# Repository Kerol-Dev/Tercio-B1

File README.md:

<div align="center">

# Tercio B1

**Brushless FOC on the Tercio bus.**

A 46 × 46 mm field-oriented-control driver for gimbal, quasi-direct-drive and hobby brushless motors.<br>
10–52 V, a 21-bit encoder on board, and the same bus, browser panel and libraries as the Tercio S1.

**Rev A is designed and 100 % routed, and its firmware runs on a simulated motor. Nothing has run on real hardware yet:<br>every rating on this page is a design target until the [bench tests](docs/08-bringup.md) confirm it.**

[Hardware](hardware/README.md) ·
[Firmware](firmware/README.md) ·
[Simulator](#simulator) ·
[Spec vs moteus](docs/02-spec-vs-x1.md) ·
[Plan](#documents)

</div>

---

## Why

A Tercio machine can already put closed-loop steppers and an IMU on one CAN bus, set up from a browser. Some joints want a brushless motor instead: gimbals that must be smooth at a crawl, legs and arms on quasi-direct-drive actuators, anything that needs torque control rather than position alone.

Good brushless controllers exist, but each comes with its own adapter, its own tools and its own library. The Tercio B1 joins the bus you already have. It speaks Tercio protocol v2 as device class 2, appears in Tercio Control next to your S1 drivers and IMUs, and is driven from the same Python and Arduino libraries. It aims at the mjbots moteus-x1 and moteus-n1 on that ecosystem and on value: a target of $99–119.

## Highlights (design targets)

| | |
|---|---|
| **On the Tercio bus** | Protocol v2, device class 2. Discovery, node IDs, parameters, telemetry and fault events work as on the S1, through the same Tercio FD adapter. |
| **21-bit encoder on board** | An MT6835 sits on the shaft axis under the board. The aux port takes an output-side encoder (SPI, I²C or quadrature), step/dir, RC PWM and a motor NTC. |
| **10–52 V, 80 V FETs** | A DRV8353RS 100 V-class gate driver with drain-source over-current protection, six 80 V / 3 mΩ BSC030N08NS5, 1 mΩ Kelvin shunts, and a regen clamp in firmware from day one. |
| **Fast loops** | PWM at 15–40 kHz (30 kHz by default), the current loop at the PWM rate, the position or velocity loop every second tick. |
| **Calibrates itself** | Measures current-sense offsets, resistance, inductance, pole pairs, direction, encoder offset and flux linkage. In simulation, R, L and flux linkage come out within 1 % on the 5010 and 2204 test motors; the gimbal's resistance reads 3.5 % high. |
| **Both bus speeds** | 500 k / 2.5 Mbit/s and 1 M / 5 Mbit/s bus profiles from the first release. |
| **Generated by code** | Schematic, placement, copper and routing are all Python that writes KiCad 10 files, authored by AI, and checked by KiCad itself: ERC 0, DRC 0, 0 schematic-parity issues. |

## Rev A board

- **46 × 46 mm, 6 layers**: 2 oz outer and 1 oz inner copper, 1.6 mm, matte black ENIG, filled and capped vias in pads.
- **Top:** the XT30 on the left edge; three half-bridges across the lower half, each low-side FET with its Kelvin shunt; phase pads A/B/C on the bottom edge; the DRV8353RS above them with its 5 V buck; CAN-in, aux and CAN-out connectors on the edges; status LEDs.
- **Bottom** (faces the motor, ≤ 2.3 mm parts): the MT6835 on the shaft axis, the STM32G431 beside the gate driver, the CAN transceiver between the connectors, SWD pads and a named test point for every rail and phase.
- **Numbers:** 163 footprints, 1,237 tracks, 340 vias, 100 % routed. BOM: 54 lines, every part in stock at JLCPCB when checked on 2026-10-13, $26.08 per board at 10 and $22.44 at 100 (components).
- **Fabrication:** `hardware/tools/jlc_fab.py` writes the gerbers, BOM and placement file for JLCPCB assembly.

## How it works

```mermaid
flowchart LR
    BUS["CAN FD bus<br/>Tercio protocol v2"] --- CAN["MCP2562FD"]
    CAN --- MCU["STM32G431<br/>FOC at 30 kHz"]
    ENC["MT6835<br/>21-bit encoder"] -- "SPI" --> MCU
    MCU -- "6 × PWM" --> DRV["DRV8353RS<br/>gate driver + 3 current amps"]
    DRV --> FET["3 half-bridges<br/>6 × BSC030N08NS5"]
    PWR["XT30<br/>10–52 V"] --> FET
    FET --> MOT(("Motor"))
    FET -. "1 mΩ Kelvin shunts" .-> DRV
    DRV -- "phase currents" --> MCU
```

- **One call per PWM period.** `FocCore` takes the ADC sample and returns the duties: Clarke and Park transforms, a d/q current controller with decoupling and latency compensation, space-vector PWM and per-tick protection. It is plain C++ with no HAL, so the same code runs on the MCU, in the unit tests and in the simulator.
- **The joint.** `Joint` runs the protocol-v2 states, the position, velocity, torque and impedance modes on the S1's trajectory planner, the regen clamp, a 1 s host deadman and temperature derating.
- **Shared with the S1.** The trajectory planner and the encoder tracker come from the S1 firmware; the CAN node and the wear-levelled settings will too ([docs/07](docs/07-firmware.md) §7.3), so the B1 behaves like the rest of the Tercio bus.

## Simulator

The firmware above, unchanged, runs at 30 kHz in real time against a model of the motor and the board.

- **The model:** a dq motor with cogging and friction, dead time, a supply that cannot sink current, 12-bit current-sense codes, the encoder's noise and timing, and the gate driver's over-current latch.
- **The page:** pick a motor, run the calibration and see what it found next to the true values, then move the joint and watch the scope at 1 kHz, or one PWM period at a time.
- **Testing:** inject faults, load the shaft, or drag the rotor by hand.

```bash
cd firmware
node simulator/server.mjs             # http://127.0.0.1:8770, builds the simulator first if needed
```

## Specifications (design targets)

| | |
|---|---|
| **Supply** | 10–52 V (3S–12S, 48 V supplies); input TVS SMCJ54A; over-voltage fault ≤ 58 V |
| **Phase current** | ~80 A peak by design; 15 A continuous without cooling as the target. Both are published only after measurement. |
| **PWM and current loop** | 15–40 kHz, 30 kHz by default |
| **MCU** | STM32G431CBT6, Arm Cortex-M4F at 170 MHz (STM32G474CBT6 as a pin-compatible alternate) |
| **Power stage** | DRV8353RS, 6 × BSC030N08NS5 (80 V, 3.0 mΩ), 1 mΩ 2512 Kelvin shunts |
| **Encoder** | MT6835, 21-bit absolute, on board |
| **Aux port** | JST-GH 8: SPI, I²C, quadrature, step/dir, RC PWM, GPIO, motor NTC, 3.3 V (PTC-limited) |
| **Bus** | CAN FD, 500 k / 2.5 Mbit/s and 1 M / 5 Mbit/s, Tercio protocol v2; 2 × JST-GH 4 for daisy chaining; 120 Ω termination by solder jumper |
| **Power connector** | XT30 (right angle) and phase solder pads |
| **Board** | 46 × 46 mm, 6 layers, height ≤ 10 mm target, ≤ 16 g target |
| **Host tools** | Tercio Control in the browser and the Python and Arduino libraries, through the Tercio FD |

The comparison with moteus-x1, n1 and r4.11 is in [docs/02](docs/02-spec-vs-x1.md).

## Building it

### Firmware

```bash
cd firmware
~/.platformio/penv/bin/pio test -e native     # host tests on simulated motors
```

### Hardware

```bash
python3 hardware/build.py                      # schematic → netlist check → ERC → PDF
python3 -I hardware/verify_bom.py              # every LCSC code checked live against JLCPCB
```

The board scripts need KiCad 10's own Python, for `pcbnew`:

```bash
KPY=/Applications/KiCad/KiCad.app/Contents/Frameworks/Python.framework/Versions/3.9/bin/python3
cd hardware
$KPY layout.py                                 # place, copper, route, fill, DRC, renders
$KPY tools/jlc_fab.py                          # build/jlc: gerbers, BOM, CPL for JLCPCB
```

The files in `hardware/kicad/` are generated: change the code and regenerate rather than editing them in KiCad. The full flow, the router and the checks are in [hardware/README.md](hardware/README.md).

## Status and next steps

| | |
|---|---|
| **Done** | Plan and decisions; rev A schematic, board and routing, DRC clean; JLC fabrication files; firmware milestone F0 (FOC core, calibration, joint) with host tests 1–6 and the real-time simulator |
| **Next** | Regen and fault-reaction tests in simulation; the CAN and protocol layer; bring-up firmware; order rev A |
| **Schedule** | Rev A order around 21 December 2026, rev B after Chinese New Year, launch around June 2027 ([docs/09](docs/09-risks-schedule.md)) |
| **Guardrail** | The Tercio S1 and FD launch on 1 December 2026 comes first: no B1 changes to the other Tercio repositories before then, and a B1 freeze from 23 November to 7 December |

## Documents

| # | Document | Contents |
|---|---|---|
| 1 | [Requirements and the wedge](docs/01-requirements.md) | Decisions, functional requirements, positioning against moteus/ODrive, rating method |
| 2 | [Spec versus moteus-x1](docs/02-spec-vs-x1.md) | Side-by-side with x1, n1 and r4.11 |
| 3 | [Part shortlist](docs/03-parts.md) | Live LCSC/JLCPCB stock and prices (2026-10-12), choices and alternates |
| 4 | [Block diagram and pin map](docs/04-architecture.md) | Power tree, STM32G431 pin map, TIM1/ADC sync, aux and CAN connectors, floor plan |
| 5 | [BOM cost and PCB plan](docs/05-bom-pcb.md) | Planning estimate ≈ $45/board at 10, ≈ $25.50 at 100 (landed); stackup and layout rules |
| 6 | [KiCad as code](docs/06-kicad-as-code.md) | Python-generated schematic and board, routing, kicad-cli checks and outputs |
| 7 | [Firmware plan](docs/07-firmware.md) | S1 architecture reuse, FOC core, calibration and identification, protocol additions, bus profiles, host simulator |
| 8 | [Bring-up and test plan](docs/08-bringup.md) | Equipment, regen handling, 14 staged tests with pass criteria |
| 9 | [Risks and schedule](docs/09-risks-schedule.md) | Risk register; 3 spins; launch ~June 2027; ≈ $4,000–4,500 to launch |

## Repository layout

```text
docs/        the plan: requirements, spec, parts, architecture, BOM, KiCad as code, firmware, bring-up, risks
data/        live part data, BOM estimate, pin map
tools/       part lookup (JLCPCB + LCSC), BOM estimate, CAN bus-time budget
hardware/
├── b1/      the Tercio B1 circuit, one module per sheet; placement, copper, routing plan, silkscreen
├── gen/     the generator: KiCad file writer, symbols, footprints, board engine, router
├── tools/   JLCPCB fabrication files, routing report, XT30 3D model
├── kicad/   the generated KiCad 10 project (open tercio-b1.kicad_pro to review)
└── lib/     IBM Plex fonts for the silkscreen (project footprints and symbols are in kicad/lib/)
firmware/
├── src/     foc/, control/, app/ (MCU and host); sim/, simulator/ (host only)
├── simulator/  Node server and web UI
└── test/    host tests
```

## Data and tools

| Path | What |
|---|---|
| `tools/parts_lookup.py` | Live JLCPCB + LCSC stock and price lookup (standard library only). Reads `tools/candidates*.txt` |
| `tools/bom_estimate.py` | BOM cost at 10/100 boards from the lookup data → `data/bom-estimate.csv` |
| `tools/can_budget.py` | CAN FD bus-time budget per node and rate (`python3 tools/can_budget.py 1000000 5000000`) |
| `data/parts-live-2026-10-12*.csv` | 686 rows of live part data from 2026-10-12 |
| `data/pinmap-g431cbt6.csv` | Pin map as a table, for the generator |

Re-run before any order (stock moves daily):

```bash
python3 -I tools/parts_lookup.py && python3 -I tools/parts_lookup.py tools/candidates-extra.txt && python3 -I tools/bom_estimate.py
```

## Decision log

Decided with Kerol on 2026-10-12:

| Topic | Decision |
|---|---|
| Power class | Smaller class first → 10–52 V (DRV8353RS makes 12S/48 V possible) |
| Peak current | Design for ~80 A peak; lead marketing with continuous current |
| Target motors | Gimbal, QDD 5010/6010, small drone/hobby BLDC |
| Price | $99–119 |
| Size | ~46 × 46 mm |
| Encoder | Onboard MT6835 (21-bit) + aux port for an output-side encoder |
| MCU | STM32G431CBT6 (G474CBT6 as a pin-compatible alternate) |
| Gate driver | DRV8353RS |
| CAN connector | 2 × JST-GH 4-pin, daisy chain |
| Power connector | 1 × XT30 + motor solder pads |
| Extras | Motor thermistor, PWM and step/dir input, spare GPIO/analog |
| USB | No (CAN only, via the FD) |
| Bus | 500k/2.5M and 1M/5M, both from the B1's first release |
| Licence | Apache-2.0 |
| Name | Tercio B1 |
| KiCad flow | Code owns everything, including routing |
| Timing | Start the schematic now, in parallel with the launch |
| S1 and the 1M/5M bus | No S1s are built yet: the shipping firmware carries the bus profile |
| Repository | Private GitHub repo Kerol-Dev/Tercio-B1 (named Tercio-bldc until 2026-10-18) |

Still open:

| Topic | Notes |
|---|---|
| Weekly time cap before launch | Yours to set; the schedule assumes part-time |
| Electrolytic on board vs on the XT30 pigtail | Height (10 mm) vs cable damping. Rev A carries a 22 µF 100 V can on board |
| Mounting-hole pattern | Check against the 5010/6010 motors on rev A |
| Retail price inside $99–119, volume tiers, starter bundle | After rev B, when the BOM and ratings are firm |

## Licence

Apache-2.0, see [LICENSE](LICENSE).

<div align="center">
<sub>Made by <a href="https://terciolabs.com">Tercio Labs</a></sub>
</div>

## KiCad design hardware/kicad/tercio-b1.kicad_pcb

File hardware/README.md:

# Tercio B1 hardware — KiCad as code

The schematic is generated by Python and checked by KiCad 10 itself. **Do not
edit the files in `kicad/` by hand.** Change the code, regenerate, and review.

```bash
cd ~/Documents/Projects/Tercio-B1 && python3 hardware/build.py
```

```bash
cd ~/Documents/Projects/Tercio-B1 && python3 -I hardware/verify_bom.py
```

`build.py` writes the KiCad project and then:

1. exports the netlist with `kicad-cli` and compares every net, pin by pin,
   with the circuit the code describes (a wire that lands on the wrong pin, or
   two nets that touch, fails the build);
2. runs ERC at all severities;
3. exports `build/tercio-b1-schematic.pdf`.

Then the board, generated with KiCad's own Python (it needs `pcbnew`):

```bash
cd ~/Documents/Projects/Tercio-B1 && /Applications/KiCad/KiCad.app/Contents/Frameworks/Python.framework/Versions/3.9/bin/python3 hardware/layout.py
```

`layout.py` loads every footprint from the KiCad netlist (reference, value, fields
and schematic path, so DRC can check schematic parity), places the fixed parts from
`b1/board.py`, auto-places the rest (courtyard- and hole-aware, per side; each part lands
on the line from the pin it serves toward where that signal goes next), draws the outline,
the power copper and planes from `b1/copper.py` and the art from `b1/art.py`, sets the
matte-black ENIG stackup and the net classes, then **routes the board**, adds the fills
(GND on F/In2/In3/B, +3V3 on In3 under the logic half), fills the zones and renders
`build/render-*.png`. `--no-route` stops after placement; `--route-only` routes the board
as placed.

```bash
cd ~/Documents/Projects/Tercio-B1/hardware && /Applications/KiCad/KiCad.app/Contents/Frameworks/Python.framework/Versions/3.9/bin/python3 layout.py --no-route && FASTROUTE_ROUNDS=30 /Applications/KiCad/KiCad.app/Contents/Frameworks/Python.framework/Versions/3.9/bin/python3 layout.py --route-only
```

### Routing

`gen/route_export.py` (KiCad's Python) turns the board and the plan in `b1/routing.py` into
flat arrays (`build/route/problem.npz` + `.json`); `gen/fastroute.py` solves them in a
separate Python 3.12 with numpy and Numba (`TERCIO_FAST_PY`, default: the NEMA23-Adapter
venv in the Tercio-s1 repo); the result comes back as ordinary locked tracks and vias.
Freerouting 2.5 left ~180 of ~300 connections unrouted here and knows nothing about gate
loops or Kelvin pairs, so the router is ours.

- 0.05 mm grid on F / In2 / In3 / B (In1 and In4 are solid GND: vias only). Widths and
  clearances per net class, exact distances plus a 0.04 mm margin, so DRC passes by
  construction. Wide classes neck down to 0.2 mm at small pads.
- Via-in-pad is allowed: JLC fills and caps vias in pads on 6-layer boards at no charge.
  Vias are 0.45/0.2 mm for logic, 0.5/0.25 gate, 0.6/0.3 supply, 0.7/0.35 power.
- Power pours are walls for other nets, except right around a connection's own pads.
- Negotiated congestion (PathFinder): every net is routed, overlaps cost more each round
  (present and history), and the nets still in conflict are routed again until nothing
  overlaps. Then legalisation drops the least important net of each remaining conflict and
  puts it back with everyone else's copper as walls; a rescue step rips up lower-priority
  nets that block what is still unrouted; anything left is promoted (within its tier) for
  another pass. Searches that run out of budget get one wider try.
- Pairs: SNx is drawn to SPx (Kelvin), the SHx return to GHx (small gate loop).

The solved routes are stored in `b1/routes.json` (`layout.py --save-routes`) and re-applied on
every regeneration, so the board rebuilds in under a minute and the router only adds what is
missing. After a placement change, move `b1/routes.json` aside and route again.

Plan and tiers (`b1/routing.py`): Kelvin pairs, gate loops, the buck's input loop (VIN → its 1 µF),
DRV supply and buck first; then a GND via per pad; +3V3 (0.25 mm), +3.3VA and the V_BUS feeds;
then the rest, shortest first. Net classes: logic and Kelvin 0.15/0.15 mm (JLC's minimum for 2 oz
outer copper, so no slack there), gate 0.2/0.2, supply 0.3/0.2, power 0.4/0.2.
A run takes about 5–10 minutes. Failures, if any, are listed in `build/route-failures.txt`.

### Silkscreen

`b1/art.py` draws it, in IBM Plex (the website's type) turned into filled polygons by
`gen/fonttext.py` from the WOFF files in `lib/fonts/` (SIL OFL, licence alongside), so nobody needs
the font installed and the gerbers carry exactly these shapes. Everything goes through a small
planner that keeps each item off pads, part bodies and footprint outlines, holes, the edge and
the other labels, searching outward from where it belongs; test-point labels must sit closer to
their own pad than to any other test point, and every test point reserves room for its label when
it is placed. Sizes stay at JLC's legend minimums or above (strokes ≥ 0.15 mm).

- Top (seen once the board is on a motor): the Tercio mark and "Tercio B1", phase letters A/B/C,
  CAN / AUX / CAN names at the connectors, "10–52 V" at the XT30, STATUS / FAULT at the LEDs.
- Bottom (bring-up): the identity with "FOC MOTOR DRIVER · 10–52 V · REV A", every test point
  named (VBUS, 5V, 3V3, 3VA, GND, SOA/SOB/SOC, GLA/GLB/GLC, SW, FLT), the SWD pad order, the
  solder jumpers (120R, NTC), CAN and AUX pinout tables, phase letters, an S/N field.

### Fabrication (JLCPCB)

```bash
cd ~/Documents/Projects/Tercio-B1/hardware && /Applications/KiCad/KiCad.app/Contents/Frameworks/Python.framework/Versions/3.9/bin/python3 tools/jlc_fab.py
```

writes `build/jlc/`: `tercio-b1-gerbers.zip` (6 copper layers, mask, paste, silk, outline,
PTH/NPTH Excellon, nothing else), `tercio-b1-bom.csv` (Comment, Designator, Footprint, LCSC),
`tercio-b1-cpl.csv` (Designator, Mid X, Mid Y, Layer, Rotation) and `ORDER.md` (order-form
settings). The gerbers follow JLC's KiCad 9 guide to the letter: X2 and netlist attributes on (JLC's
parser reads the layer functions and the board profile from them; with X2 off the upload came back
with no layers or size), absolute coordinates, Protel extensions, PTH and NPTH separate. BOM and CPL
come from the routed board, so they agree with each other and the gerbers. CPL positions are pad
centres in the gerbers' absolute coordinates; rotation is KiCad's angle (top) or 180° − angle (bottom) plus a per-package
zero-orientation correction from the community table kept with the Fabrication Toolkit plugin
(the same formula as Bouni's kicad-jlcpcb-tools). Packages without an entry are listed in
`ORDER.md` to confirm in JLC's placement preview.

`verify_bom.py` exports the JLC BOM (`build/bom-jlc.csv`) and checks every
LCSC code live against JLCPCB: it must exist, match the value and package,
and have stock for the build. It also reports today's component cost.

State at rev A generation (2026-10-13):

| Check | Result |
|---|---|
| Netlist vs intent | 104 nets match; 12 no-connects, all intentional |
| ERC (all severities) | 0 violations |
| DRV8353RS symbol vs TI pin table | 48/48 pins match |
| MT6835 symbol vs MagnTek pin table | 16/16 pins match |
| BOM | 54 lines, 24 Extended, all codes valid and in stock; $26.08/board at 10, $22.44 at 100 (components) |
| Independent review (2026-10-12) | No critical findings; 4 major + 7 minor fixed (VDRAIN/VM filters, SMCJ54A, 50 mA aux PTC, 5.0 V FB, MT6835 TEST, 1 A inductor, 1.5k SDO pull-up, 10 µF bulk MLCC) |
| Board | 163 footprints, 6 layers, **100 % routed** (1,237 tracks, 340 vias, `b1/routes.json`); KiCad DRC at all severities (silkscreen included): 0 violations, 0 unconnected, 0 schematic-parity issues |
| Fabrication | `tools/jlc_fab.py`: gerbers + drill, BOM (54 lines) and CPL (122 parts: 48 top, 74 bottom) for JLCPCB |

## Layout of the code

| Path | What |
|---|---|
| `gen/sexpr.py` | S-expression reader/writer for KiCad files |
| `gen/symbols.py` | Loads KiCad 10's symbol libraries (flattens derived symbols), pin geometry, `make_ic` for code-defined symbols |
| `gen/model.py` | Circuit model: sheets, parts, pin→net assignments; every visible pin must be assigned or marked `NC` |
| `gen/writer.py` | Model → `.kicad_sch`/`.kicad_pro`, project symbol library; deterministic UUIDs |
| `gen/footprints.py` | Project footprints (Kelvin 2512 shunt with net-tie sense pads, motor phase pad) |
| `gen/custom.py` | DRV8353RS and MT6835 symbols, from the vendor pin tables |
| `gen/catalog.py` | Footprints and LCSC codes (JLC Basic where possible) |
| `b1/*.py` | The Tercio B1 circuit, one module per sheet, with design notes on each sheet |
| `gen/pcb.py` | Board engine (KiCad Python): netlist → footprints, placement with collision search, zones, vias, tracks |
| `gen/router.py` | Board geometry and clearance rasters for the router (the first, slower router lives on here too) |
| `gen/route_export.py`, `gen/fastroute.py` | Routing problem export (KiCad Python) and the Numba negotiated-congestion router |
| `b1/routing.py` | Routing plan: tiers and order, pairs |
| `tools/route_report.py` | Routing review: per-net length / vias / layers for the critical classes, per-layer copper plots |
| `b1/board.py`, `b1/copper.py`, `b1/art.py` | Placement plan, power copper and planes, silkscreen (planner + design) |
| `gen/fonttext.py`, `lib/fonts/` | IBM Plex outlines (WOFF, SIL OFL) → silkscreen polygons |
| `tools/jlc_fab.py` | JLCPCB gerbers, BOM and CPL with rotation corrections |
| `tools/xt30pw_model.py` | CadQuery model of the XT30PW-M (KiCad 10 ships none) |
| `build.py`, `layout.py`, `verify_bom.py` | Generate and check |
| `kicad/` | Generated KiCad project (open `tercio-b1.kicad_pro` in KiCad 10 to review) |
| `build/` | Netlist, ERC report, PDF, BOM (git-ignored) |

## Sheets

| Page | Sheet | Refs |
|---|---|---|
| 2 | Power input and rails: XT30, TVS, bulk, V_BUS sense, 3.3 V LDO, +3.3VA filter, test points, holes | 1xx |
| 3 | Gate driver and buck: DRV8353RS, VDRAIN filter, charge pump, LM5008A buck (+5V), SPI/fault/enable pulls, bring-up test points | 2xx |
| 4 | Power stage: 3 half-bridges, Kelvin shunts, gate resistors, DNP snubbers, bulk bank, FET NTC, DNP phase-voltage taps | 3xx |
| 5 | MCU: STM32G431CBT6, decoupling, HSE, reset/BOOT0, SWD pads (1×5, S1/FD order), LEDs, ADC front-end, SPI source termination | 4xx |
| 6 | Encoder: MT6835 (CAL_EN on PC15) | 5xx |
| 7 | CAN-FD: MCP2562FD, ESD, split termination (solder jumper), 2 × JST-GH 4 | 6xx |
| 8 | Aux port: JST-GH 8, series R, ESD, PTC 3V3, motor-NTC pull-up | 7xx |

## Review workflow

Open `kicad/tercio-b1.kicad_pro` in KiCad 10 (or read `build/tercio-b1-schematic.pdf`).
Write findings down. Fixes go into `b1/*.py`, and then you regenerate. Edits made
in KiCad are overwritten by the next build, by design ("code owns everything").

## Board (rev A) at a glance

- 46 × 46 mm, 6 layers (2 oz outer / 1 oz inner), 1.6 mm, matte black mask, white silk, ENIG,
  filled and capped vias in pads.
- Top: XT30 on the left edge, three half-bridges across the bottom half (high-side over low-side,
  Kelvin shunt beside each low-side FET, 10 µF 100 V bulk in slots around them), phase pads A/B/C
  on the bottom edge, DRV8353RS centred above the legs with its buck, 22 µF 100 V can, right-angle
  JST-GH connectors with their cable entries at the edges (CAN-in GH-4 top left, aux GH-8 top
  right, CAN-out GH-4 on the right edge), status LEDs.
- Bottom (≤ 2.3 mm parts, faces the motor): MT6835 on the shaft axis (turned 180° so its SPI pins
  face the MCU); the MCU beside the DRV, rotated 180° so its PWM / chip-select pins face the DRV's
  control pins across a 3 mm via lane and its aux pins face the aux connector; CAN transceiver
  between the CAN connectors, LDO, logic passives, SWD pads, test points, input TVS, the Tercio mark.
- Copper: In1 and In4 solid GND; In2 V_BUS under the power half (a finger up to the XT30), a phase
  pour per leg down to its pad, signals and GND fill elsewhere; In3 signals, then +3V3 fill under
  the logic half and GND fill under the power half; per-leg V_BUS / phase / LSRC / GND-return pours
  on top; phase pours on the bottom.
- Next: upload `build/jlc/` to JLC for the quote, check the parts listed in `ORDER.md` in the placement preview.

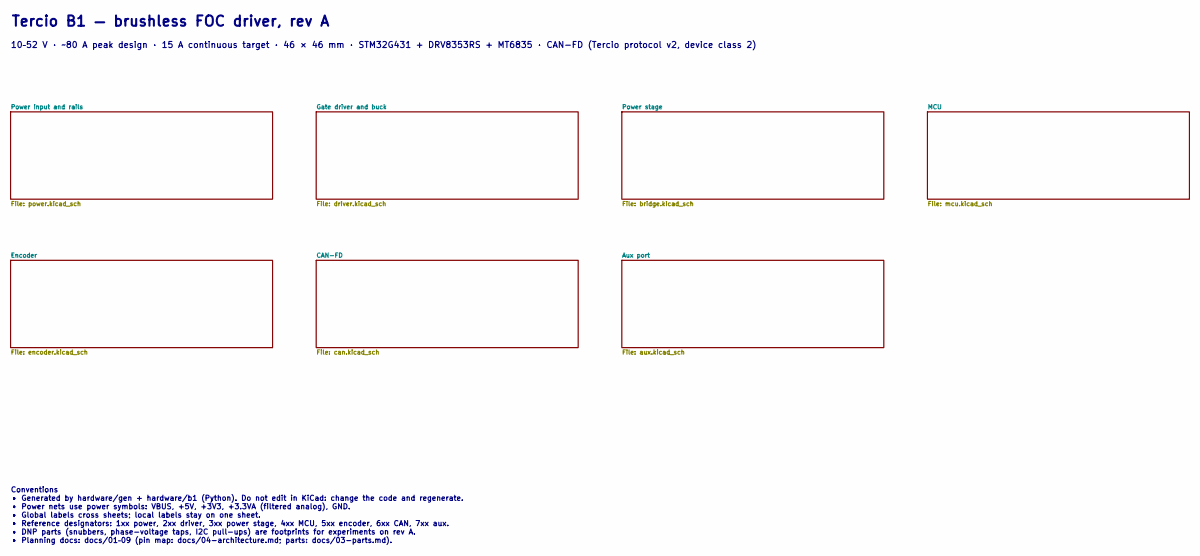
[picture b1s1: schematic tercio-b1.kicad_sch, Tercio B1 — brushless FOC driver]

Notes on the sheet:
Tercio B1 — brushless FOC driver, rev A
10–52 V · ~80 A peak design · 15 A continuous target · 46 × 46 mm · STM32G431 + DRV8353RS + MT6835 · CAN-FD (Tercio protocol v2, device class 2)
Conventions • Generated by hardware/gen + hardware/b1 (Python). Do not edit in KiCad: change the code and regenerate. • Power nets use power symbols: VBUS, +5V, +3V3, +3.3VA (filtered analog), GND. • Global labels cross sheets; local labels stay on one sheet. • Reference designators: 1xx power, 2xx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

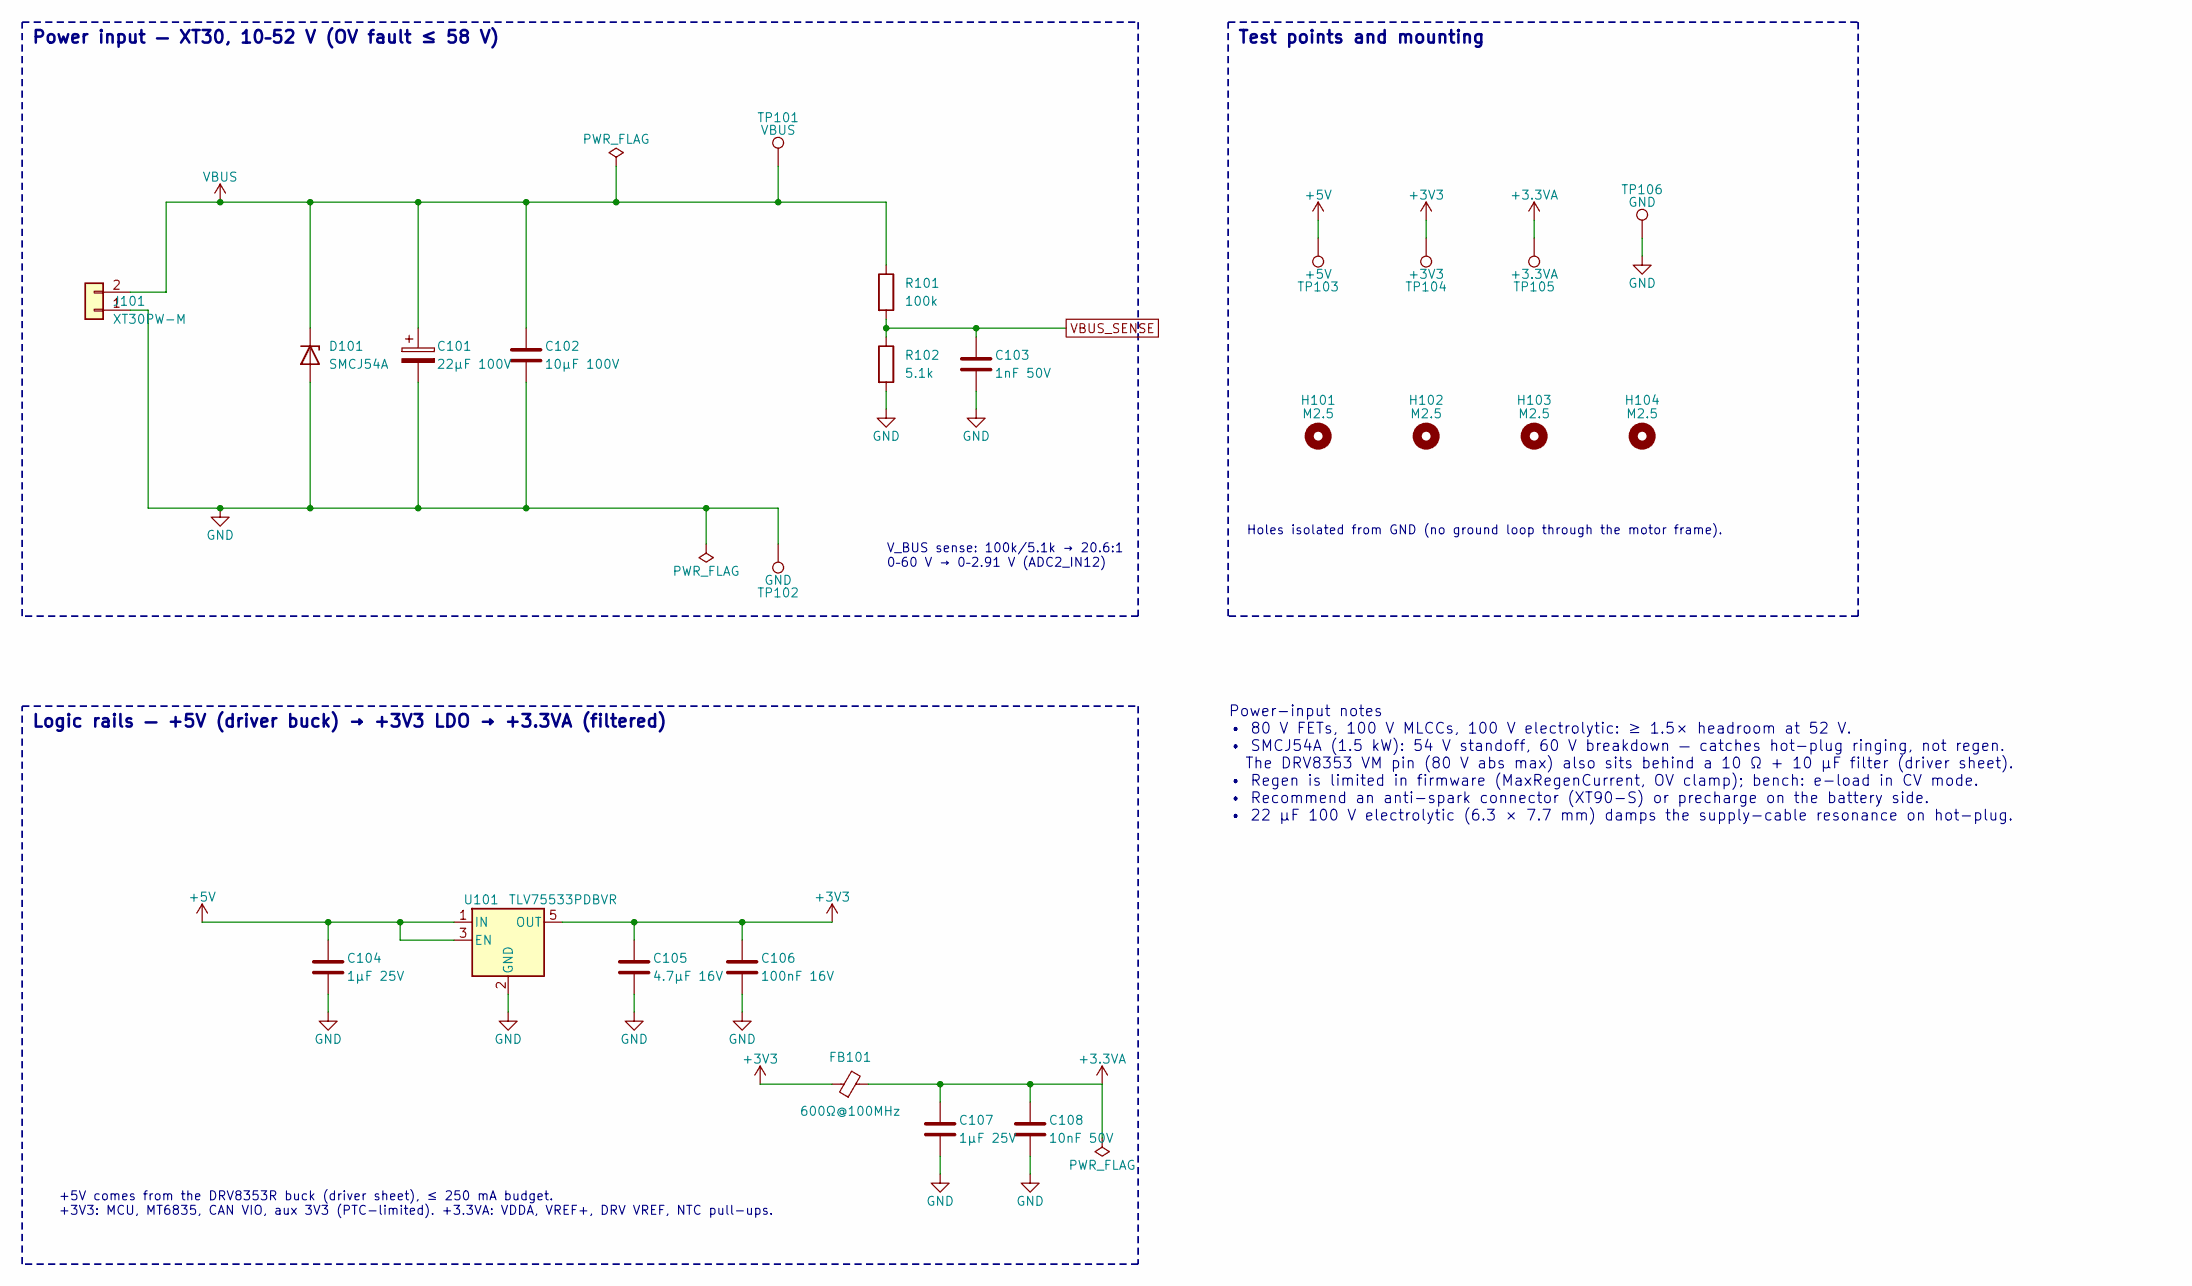
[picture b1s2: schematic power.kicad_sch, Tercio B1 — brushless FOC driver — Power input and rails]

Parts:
C101: 22µF 100V; CP_Elec_6.3x7.7; MPN JVJ100V22M6x8; LCSC C46550391
C102: 10µF 100V; C_1210_3225Metric; LCSC C5156756
C103: 1nF 50V; C_0402_1005Metric; LCSC C1523
C104, C107: 1µF 25V; C_0402_1005Metric; LCSC C52923
C105: 4.7µF 16V; C_0603_1608Metric; LCSC C19666
C106: 100nF 16V; C_0402_1005Metric; LCSC C1525
C108: 10nF 50V; C_0402_1005Metric; LCSC C15195
D101: SMCJ54A; D_SMC; MPN SMCJ54A; LCSC C438116
FB101: 600Ω@100MHz; L_0603_1608Metric; MPN GZ1608D601TF; LCSC C1002
H101, H102, H103, H104: M2.5; MountingHole_2.7mm_M2.5
J101: XT30PW-M; AMASS_XT30PW-M_1x02_P2.50mm_Horizontal; MPN XT30PW-M30.G.Y; LCSC C431092
R101: 100k; R_0603_1608Metric; LCSC C25803
R102: 5.1k; R_0402_1005Metric; LCSC C25905
TP101: VBUS; TestPad_D0.9mm
TP102, TP106: GND; TestPad_D0.9mm
TP103: +5V; TestPad_D0.9mm
TP104: +3V3; TestPad_D0.9mm
TP105: +3.3VA; TestPad_D0.9mm
U101: TLV75533PDBVR; SOT-23-5; MPN TLV75533PDBVR; LCSC C404027

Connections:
+3.3VA: C107.1, C108.1, FB101.2, TP105.1; also elsewhere on the board
+3V3: C105.1, C106.1, FB101.1, TP104.1, U101.5 (OUT); also elsewhere on the board
+5V: C104.1, TP103.1, U101.1 (IN), U101.3 (EN); also elsewhere on the board
GND: C101.2, C102.2, C103.2, C104.2, C105.2, C106.2, C107.2, C108.2, D101.2 (A), J101.1, R102.2, TP102.1, TP106.1, U101.2 (GND); also elsewhere on the board
VBUS: C101.1, C102.1, D101.1 (K), J101.2, R101.1, TP101.1; also elsewhere on the board
VBUS_SENSE: C103.1, R101.2, R102.1; also elsewhere on the board

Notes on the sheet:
Power input — XT30, 10–52 V (OV fault ≤ 58 V)
Logic rails — +5V (driver buck) → +3V3 LDO → +3.3VA (filtered)
Test points and mounting
V_BUS sense: 100k/5.1k → 20.6:1 0–60 V → 0–2.91 V (ADC2_IN12)
+5V comes from the DRV8353R buck (driver sheet), ≤ 250 mA budget. +3V3: MCU, MT6835, CAN VIO, aux 3V3 (PTC-limited). +3.3VA: VDDA, VREF+, DRV VREF, NTC pull-ups.
Holes isolated from GND (no ground loop through the motor frame).
Power-input notes • 80 V FETs, 100 V MLCCs, 100 V electrolytic: ≥ 1.5× headroom at 52 V. • SMCJ54A (1.5 kW): 54 V standoff, 60 V breakdown — catches hot-plug ringing, not regen. The DRV8353 VM pin (80 V abs max) also sits behind a 10 Ω + 10 µF filter (driver sheet). • Regen is limited in firmware (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

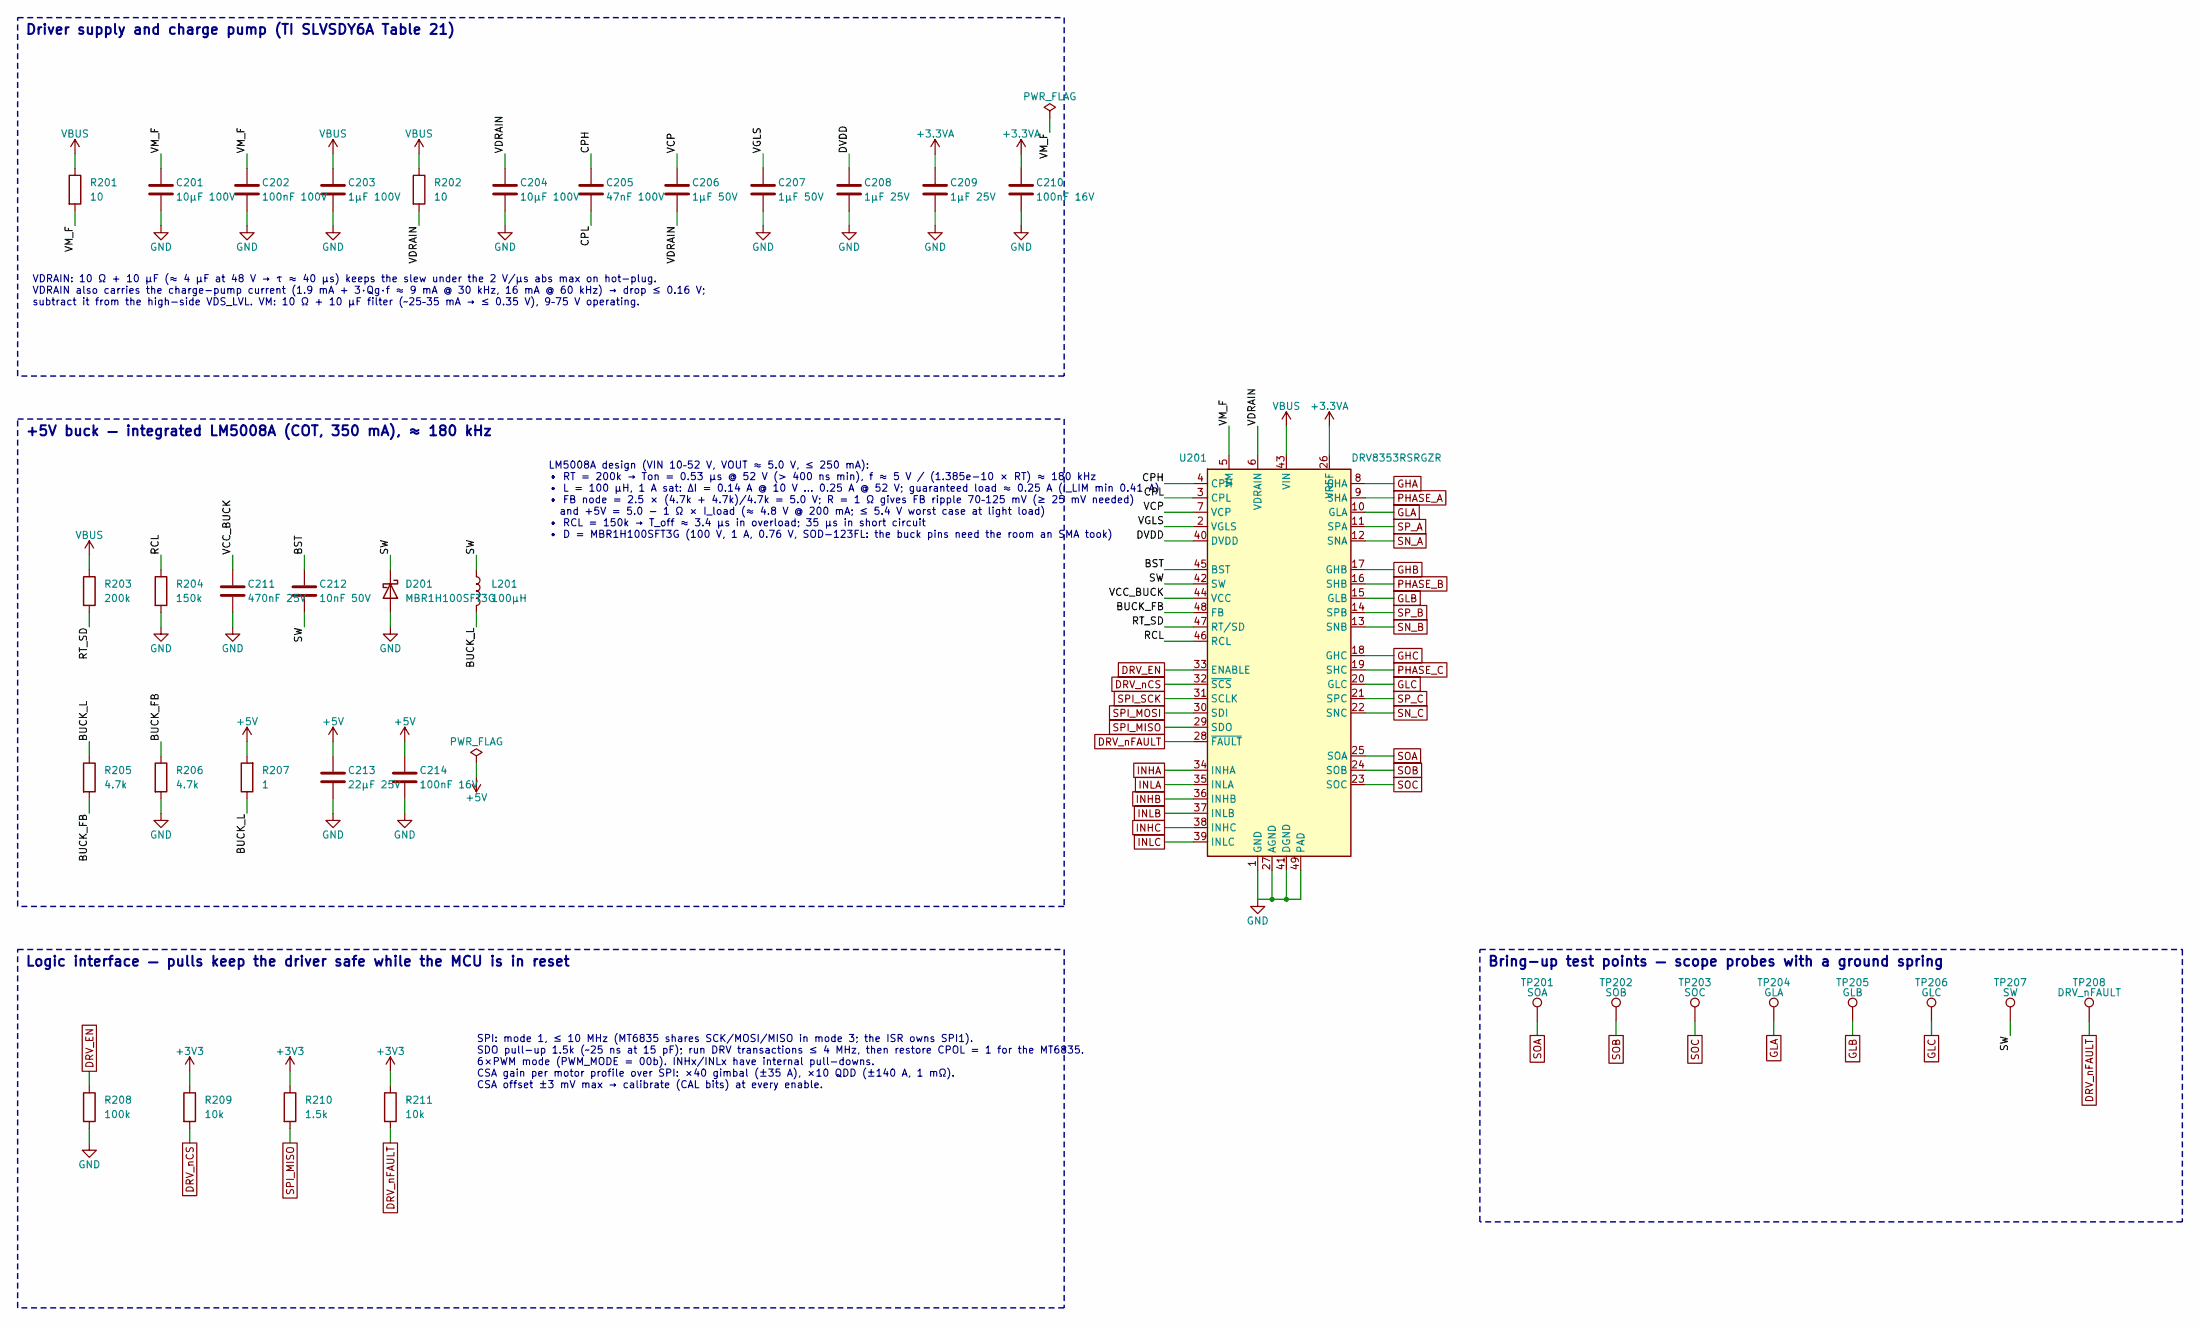
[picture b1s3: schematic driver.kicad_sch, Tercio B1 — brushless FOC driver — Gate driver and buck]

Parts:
C201, C204: 10µF 100V; C_1210_3225Metric; LCSC C5156756
C202: 100nF 100V; C_0603_1608Metric; LCSC C15725
C203: 1µF 100V; C_0805_2012Metric; LCSC C5370002
C205: 47nF 100V; C_0603_1608Metric; LCSC C576852
C206, C207: 1µF 50V; C_0603_1608Metric; LCSC C15849
C208, C209: 1µF 25V; C_0402_1005Metric; LCSC C52923
C210, C214: 100nF 16V; C_0402_1005Metric; LCSC C1525
C211: 470nF 25V; C_0603_1608Metric; LCSC C1623
C212: 10nF 50V; C_0402_1005Metric; LCSC C15195
C213: 22µF 25V; C_0805_2012Metric; LCSC C45783
D201: MBR1H100SFT3G; D_SOD-123F; MPN MBR1H100SFT3G; LCSC C235757
L201: 100µH; L_Sunlord_SWPA6045S; MPN SWPA6045S101MT; LCSC C60633
R201, R202: 10; R_0603_1608Metric; LCSC C22859
R203: 200k; R_0603_1608Metric; LCSC C25811
R204: 150k; R_0603_1608Metric; LCSC C22807
R205, R206: 4.7k; R_0402_1005Metric; LCSC C25900
R207: 1; R_0805_2012Metric; LCSC C25271
R208: 100k; R_0402_1005Metric; LCSC C25741
R209, R211: 10k; R_0402_1005Metric; LCSC C25744
R210: 1.5k; R_0402_1005Metric; LCSC C25867
TP201: SOA; TestPad_D0.9mm
TP202: SOB; TestPad_D0.9mm
TP203: SOC; TestPad_D0.9mm
TP204: GLA; TestPad_D0.9mm
TP205: GLB; TestPad_D0.9mm
TP206: GLC; TestPad_D0.9mm
TP207: SW; TestPad_D0.9mm
TP208: DRV_nFAULT; TestPad_D0.9mm
U201: DRV8353RSRGZR; Texas_RGZ0048A_VQFN-48-1EP_7x7mm_P0.5mm_EP5.15x5.15mm_Therm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; MPN DRV8353RSRGZR; LCSC C506246

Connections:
+3.3VA: C209.1, C210.1, U201.26 (VREF); also elsewhere on the board
+3V3: R209.1, R210.1, R211.1; also elsewhere on the board
+5V: C213.1, C214.1, R207.2; also elsewhere on the board
/Gate driver and buck/BST: C212.1, U201.45 (BST)
/Gate driver and buck/BUCK_FB: R205.2, R206.1, U201.48 (FB)
/Gate driver and buck/BUCK_L: L201.2, R205.1, R207.1
/Gate driver and buck/CPH: C205.1, U201.4 (CPH)
/Gate driver and buck/CPL: C205.2, U201.3 (CPL)
/Gate driver and buck/DVDD: C208.1, U201.40 (DVDD)
/Gate driver and buck/RCL: R204.1, U201.46 (RCL)
/Gate driver and buck/RT_SD: R203.2, U201.47 (RT/SD)
/Gate driver and buck/SW: C212.2, D201.1 (K), L201.1, TP207.1, U201.42 (SW)
/Gate driver and buck/VCC_BUCK: C211.1, U201.44 (VCC)
/Gate driver and buck/VCP: C206.1, U201.7 (VCP)
/Gate driver and buck/VDRAIN: C204.1, C206.2, R202.2, U201.6 (VDRAIN)
/Gate driver and buck/VGLS: C207.1, U201.2 (VGLS)
/Gate driver and buck/VM_F: C201.1, C202.1, R201.2, U201.5 (VM)
DRV_EN: R208.1, U201.33 (ENABLE); also elsewhere on the board
DRV_nCS: R209.2, U201.32 (~SCS); also elsewhere on the board
DRV_nFAULT: R211.2, TP208.1, U201.28 (~FAULT); also elsewhere on the board
GHA: U201.8 (GHA); also elsewhere on the board
GHB: U201.17 (GHB); also elsewhere on the board
GHC: U201.18 (GHC); also elsewhere on the board
GLA: TP204.1, U201.10 (GLA); also elsewhere on the board
GLB: TP205.1, U201.15 (GLB); also elsewhere on the board
GLC: TP206.1, U201.20 (GLC); also elsewhere on the board
GND: C201.2, C202.2, C203.2, C204.2, C207.2, C208.2, C209.2, C210.2, C211.2, C213.2, C214.2, D201.2 (A), R204.2, R206.2, R208.2, U201.1 (GND), U201.27 (AGND), U201.41 (DGND), U201.49 (PAD); also elsewhere on the board
INHA: U201.34 (INHA); also elsewhere on the board
INHB: U201.36 (INHB); also elsewhere on the board
INHC: U201.38 (INHC); also elsewhere on the board
INLA: U201.35 (INLA); also elsewhere on the board
INLB: U201.37 (INLB); also elsewhere on the board
INLC: U201.39 (INLC); also elsewhere on the board
PHASE_A: U201.9 (SHA); also elsewhere on the board
PHASE_B: U201.16 (SHB); also elsewhere on the board
PHASE_C: U201.19 (SHC); also elsewhere on the board
SN_A: U201.12 (SNA); also elsewhere on the board
SN_B: U201.13 (SNB); also elsewhere on the board
SN_C: U201.22 (SNC); also elsewhere on the board
SOA: TP201.1, U201.25 (SOA); also elsewhere on the board
SOB: TP202.1, U201.24 (SOB); also elsewhere on the board
SOC: TP203.1, U201.23 (SOC); also elsewhere on the board
SPI_MISO: R210.2, U201.29 (SDO); also elsewhere on the board
SPI_MOSI: U201.30 (SDI); also elsewhere on the board
SPI_SCK: U201.31 (SCLK); also elsewhere on the board
SP_A: U201.11 (SPA); also elsewhere on the board
SP_B: U201.14 (SPB); also elsewhere on the board
SP_C: U201.21 (SPC); also elsewhere on the board
VBUS: C203.1, R201.1, R202.1, R203.1, U201.43 (VIN); also elsewhere on the board

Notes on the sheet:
Driver supply and charge pump (TI SLVSDY6A Table 21)
+5V buck — integrated LM5008A (COT, 350 mA), ≈ 180 kHz
Logic interface — pulls keep the driver safe while the MCU is in reset
Bring-up test points — scope probes with a ground spring
VDRAIN: 10 Ω + 10 µF (≈ 4 µF at 48 V → τ ≈ 40 µs) keeps the slew under the 2 V/µs abs max on hot-plug. VDRAIN also carries the charge-pump current (1.9 mA + 3·Qg·f ≈ 9 mA @ 30 kHz, 16 mA @ 60 kHz) → drop ≤ 0.16 V; subtract it from the high-side VDS_LVL. VM: 10 Ω + 10 µF filter (~25–35 mA → ≤ 0.35 V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
LM5008A design (VIN 10–52 V, VOUT ≈ 5.0 V, ≤ 250 mA): • RT = 200k → Ton = 0.53 µs @ 52 V (> 400 ns min), f ≈ 5 V / (1.385e-10 × RT) ≈ 180 kHz • L = 100 µH, 1 A sat: ΔI = 0.14 A @ 10 V … 0.25 A @ 52 V; guaranteed load ≈ 0.25 A (I_LIM min 0.41 A) • FB node = 2.5 × (4.7k + 4.7k)/4.7k = 5.0 V; R = 1 Ω 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
SPI: mode 1, ≤ 10 MHz (MT6835 shares SCK/MOSI/MISO in mode 3; the ISR owns SPI1). SDO pull-up 1.5k (~25 ns at 15 pF); run DRV transactions ≤ 4 MHz, then restore CPOL = 1 for the MT6835. 6×PWM mode (PWM_MODE = 00b). INHx/INLx have internal pull-downs. CSA gain per motor profile over SPI: ×40 gimbal 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

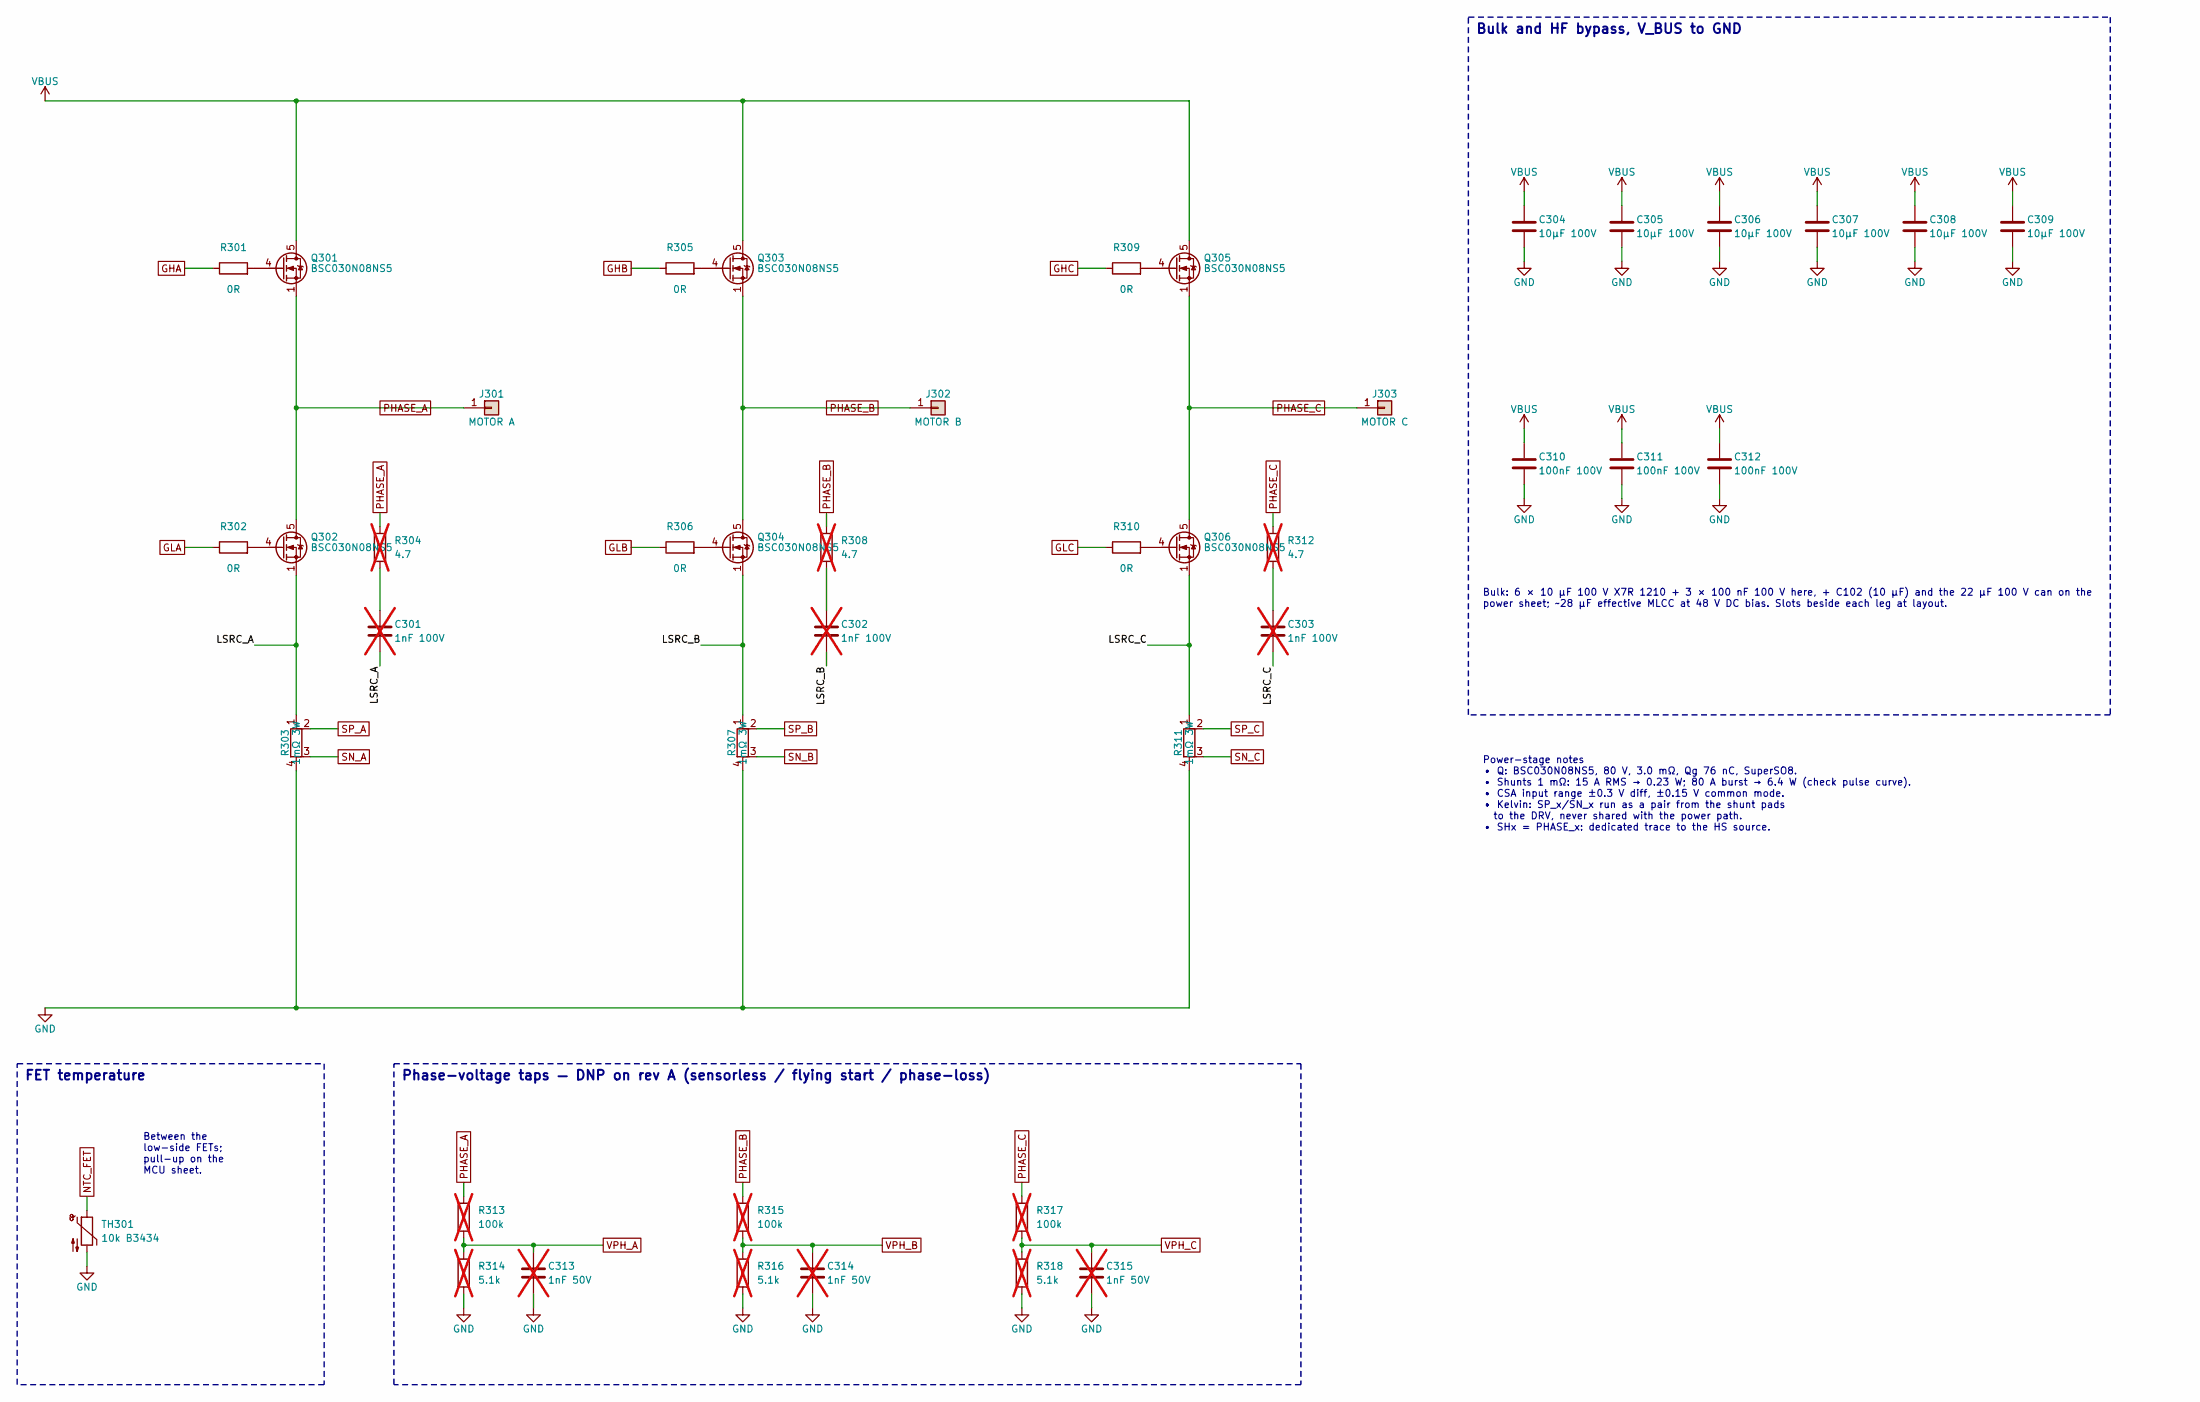
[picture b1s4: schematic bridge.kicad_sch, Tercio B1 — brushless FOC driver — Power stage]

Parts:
C301, C302, C303: 1nF 100V; C_0603_1608Metric; not fitted
C304, C305, C306, C307, C308, C309: 10µF 100V; C_1210_3225Metric; LCSC C5156756
C310, C311, C312: 100nF 100V; C_0805_2012Metric; LCSC C28233
C313, C314, C315: 1nF 50V; C_0402_1005Metric; not fitted
J301: MOTOR A; MotorPad_3.6x6mm
J302: MOTOR B; MotorPad_3.6x6mm
J303: MOTOR C; MotorPad_3.6x6mm
Q301, Q302, Q303, Q304, Q305, Q306: BSC030N08NS5; TDSON-8-1; MPN BSC030N08NS5; LCSC C501507
R301, R302, R305, R306, R309, R310: 0R; R_0402_1005Metric; LCSC C17168
R303, R307, R311: 1mΩ 3W; R_2512_Kelvin; MPN RLP25FEGR001; LCSC C459678
R304, R308, R312: 4.7; R_0805_2012Metric; not fitted
R313, R315, R317: 100k; R_0603_1608Metric; not fitted
R314, R316, R318: 5.1k; R_0402_1005Metric; not fitted
TH301: 10k B3434; R_0603_1608Metric; MPN NCP18XH103F03RB; LCSC C13564

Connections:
/Power stage/LSRC_A: C301.2, Q302.1 (S), Q302.2 (S), Q302.3 (S), R303.1
/Power stage/LSRC_B: C302.2, Q304.1 (S), Q304.2 (S), Q304.3 (S), R307.1
/Power stage/LSRC_C: C303.2, Q306.1 (S), Q306.2 (S), Q306.3 (S), R311.1
GHA: R301.1; also elsewhere on the board
GHB: R305.1; also elsewhere on the board
GHC: R309.1; also elsewhere on the board
GLA: R302.1; also elsewhere on the board
GLB: R306.1; also elsewhere on the board
GLC: R310.1; also elsewhere on the board
GND: C304.2, C305.2, C306.2, C307.2, C308.2, C309.2, C310.2, C311.2, C312.2, C313.2, C314.2, C315.2, R303.4, R307.4, R311.4, R314.2, R316.2, R318.2, TH301.2; also elsewhere on the board
NTC_FET: TH301.1; also elsewhere on the board
unnamed: C301.1, R304.2
unnamed: C302.1, R308.2
unnamed: C303.1, R312.2
unnamed: Q301.4 (G), R301.2
unnamed: Q302.4 (G), R302.2
unnamed: Q303.4 (G), R305.2
unnamed: Q304.4 (G), R306.2
unnamed: Q305.4 (G), R309.2
unnamed: Q306.4 (G), R310.2
PHASE_A: J301.1, Q301.1 (S), Q301.2 (S), Q301.3 (S), Q302.5 (D), R304.1, R313.1; also elsewhere on the board
PHASE_B: J302.1, Q303.1 (S), Q303.2 (S), Q303.3 (S), Q304.5 (D), R308.1, R315.1; also elsewhere on the board
PHASE_C: J303.1, Q305.1 (S), Q305.2 (S), Q305.3 (S), Q306.5 (D), R312.1, R317.1; also elsewhere on the board
SN_A: R303.3; also elsewhere on the board
SN_B: R307.3; also elsewhere on the board
SN_C: R311.3; also elsewhere on the board
SP_A: R303.2; also elsewhere on the board
SP_B: R307.2; also elsewhere on the board
SP_C: R311.2; also elsewhere on the board
VBUS: C304.1, C305.1, C306.1, C307.1, C308.1, C309.1, C310.1, C311.1, C312.1, Q301.5 (D), Q303.5 (D), Q305.5 (D); also elsewhere on the board
VPH_A: C313.1, R313.2, R314.1; also elsewhere on the board
VPH_B: C314.1, R315.2, R316.1; also elsewhere on the board
VPH_C: C315.1, R317.2, R318.1; also elsewhere on the board

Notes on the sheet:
Bulk and HF bypass, V_BUS to GND
FET temperature
Phase-voltage taps — DNP on rev A (sensorless / flying start / phase-loss)
Bulk: 6 × 10 µF 100 V X7R 1210 + 3 × 100 nF 100 V here, + C102 (10 µF) and the 22 µF 100 V can on the power sheet; ~28 µF effective MLCC at 48 V DC bias. Slots beside each leg at layout.
Between the low-side FETs; pull-up on the MCU sheet.
Power-stage notes • Q: BSC030N08NS5, 80 V, 3.0 mΩ, Qg 76 nC, SuperSO8. • Shunts 1 mΩ: 15 A RMS → 0.23 W; 80 A burst → 6.4 W (check pulse curve). • CSA input range ±0.3 V diff, ±0.15 V common mode. • Kelvin: SP_x/SN_x run as a pair from the shunt pads to the DRV, never shared with the power path. • 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

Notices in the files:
README.md:
License: Apache-2.0
